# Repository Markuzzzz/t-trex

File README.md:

# t-trex
Python based quadruped robot powered by Raspberry Pi Zero 2 W

# nifty-inspirations
Nifty Projects - because simple solutions are hard to find!

## Description

t-trex for Raspberry Pi is based on the [Sunfounder Remote Control Crawling Robot](https://www.elektormagazine.com/news/review-sunfounder-remote-control-crawling-quadruped-robot-v2-0) by panerqiang@sunfounder.com, which was the main starting point of the Python code for this project. Especially the calculations related to kinematics of the legs was very helpful. [Regis Hsu](https://www.instructables.com/DIY-Spider-RobotQuad-robot-Quadruped/) on his turn created an amazing 3D printed Quadruped frame which was also based on the Sunfounder project. t-trex is fundamentally built on the work of these two projects to jumpstart and extend with new features. The code written in C was ported to Python and fully refactored, because this programming language is focussed more on the ease of development. So easy to step in for beginners. And when Python is not fast enough (like compiled C code is), it can be combined with the low level C-language. Python is also very popular in the AI community and embedded solutions, resulting in massive amount of libraries to your disposal. Last but not least, Python is also very well supported by the Raspberry Pi ecosystem. 

More to come soon, as I will upload resources to github!

## Features
- Fully Python 3 compatible

- Remote SSH over Wifi support

- PS4 Controller support ([python-evdev](https://python-evdev.readthedocs.io/en/latest/))
    * Crawling Gait Control
    * Speed up/down movements
    * Graceful Quit Program Hard Shutdown (mode 1 soft shutdown)
    * Rumble support
    * System report (mode 1 default stance)

- Different Crwaling Gaits implemented
    * Forward 
    * Backward
    * Left
    * Right
    * Stand (mode 1 head up)
    * Sit (mode 1 head down)
    * Head up/down

- PiJuice Zero Hat
    * Monitoring by PiJuice Zero for save shutdown on low battery voltage
    * custom led usage for simple messages
    * custom switch support for shutting down RPi OS 

- Systemd bootable service (sequence)
    * Logging to System Journal
    * Automatic reconnect at startup
    * Graceful Shutdown sequence on exception

To do
- Interruptable actions
- Advanced movements using analog joysticks
- AI Supervised Neural Net

# Video's of the different build phases
Phase 1: Re-creating Regis Hsu quadruped setup with the Arduino code.

https://user-images.githubusercontent.com/20856694/191291677-cc345581-42a2-487b-9b4e-a81b1ac22a6e.mov

Phase 2: Redesigned model and converted Arduino code to Python
#todo add

## Hardware Configuration
At the heart of this robot runs a RPi Zero W 2 as main cpu. Its controls 12 SG90 micro servo’s distributed over 4 legs using a I2C Servo PWM Pi (made by ABElectronics). To drive the power hungry micro servo’s, the power system consists of two separate power supplies to prevent voltage dips. One dedicated 1S LiPo @ 500 mAh for the RPi, fully managed by a PiJuice module on top of the RPi. Which is also able to charge the LiPo in place by USB or solar power source. The micro servo’s have their own power supply using a 2S LiPo @ 1300 mAh through a 5V buck converter for heavy duty action.

## Components
[Raspberry Pi Zero 2 W](https://www.raspberrypi.com/products/raspberry-pi-zero-2-w/) - the heart of the quadruped robot

[Servo PWM Driver Pi Zero](https://www.abelectronics.co.uk/p/72/servo-pwm-pi-zero) - Servo driver for all 12 servo's

[SG90 Servo](https://www.kiwi-electronics.com/nl/micro-servo-sg90-1-8kg-cm-9g-3018) - Servo type used

[UBEC DC/DC Step-Down Buck Converter - 5V/3A](https://www.kiwi-electronics.com/nl/ubec-dc-dc-step-down-buck-converter-5v-3a-output-9976) - Stepping down 2S 7.8V to 5V converter used for the 12 servo's and servo driver

[Pi-Juice Zero Hat](https://github.com/PiSupply/PiJuice) - Uninterruptable Power Supply (UPS) for the raspberry pi only, to ensure correct execution

[2S LiPo 1300 mAh](https://www.velleman.eu/products/view/?id=434062) - Battery used for servo system with built-in Battery Management System (BMS)

[1S LiPo 500 mAh](https://uk.pi-supply.com/products/lithium-ion-polymer-battery-3-7v-500mah) - Battery used for PiJuice and Raspberry Pi Zero 2 W with BMS

## Body Framework
The body is based on the work of [Regis Hsu](https://www.instructables.com/DIY-Spider-RobotQuad-robot-Quadruped/). To fit my chosen LiPo batteries, I altered his model. This is added to the design models.

## Installation
[Setup Pi Zero 2 W](https://desertbot.io/blog/headless-raspberry-pi-zero-w-2-ssh-wifi-setup-mac-windows-10-steps) - how to setup a headless RPi, this project uses Raspbian OS Lite Legacy 2022-01-28

```bash
# Python3 setup
sudo apt install -y python3-dev
sudo apt install -y python3-smbus i2c-tools
sudo apt install -y python3-pil
sudo apt install -y python3-pip
sudo apt install -y python3-setuptools
sudo apt install -y python3-rpi.gpio

# Evdev 
sudo pip install evdev

# Pijuice Zero
sudo apt-get install pijuice-base

# Servo driver library
git clone https://github.com/abelectronicsuk/ABElectronics_Python_Libraries.git
sudo python3 setup.py install

# PS4 Controller
sudo apt-get install joystick
```

## Additional Commands
```bash
# Increase Swap file 
df -Bm # check free space available
sudo dphys-swapfile swapoff
sudo nano /etc/dphys-swapfile
# Change Swap size
sudo dphys-swapfile setup
sudo dphys-swapfile swapon
sudo reboot now

# Prevent ssh ‘hang’ in terminal
Host ttrex.local
  HostName ttrex.local
  User markus
  ServerAliveInterval 10

# SSH connection set in terminal per server 
Sudo nano ~/.ssh/config
Host keepsdroppingme.com
   ServerAliveInterval 10

For killing it when it gets hang up, you can use the ssh escape character: ~.

# Connect to bluetooth controller
sudo bluetoothctl
agent on
discoverable on
pairable on
default-agent

Scan on
Pair <device id>
Trust <device id>
Connect <device id>

if not connecting, remove first!

# evdev testing
python3 /usr/local/lib/python3.9/dist-packages/evdev/evtest.py
Or
python3 -m evdev.evtest

# i2c commands
# change speed
sudo nano /boot/config.txt
dtparam=i2c_arm=on,i2c_arm_baudrate=200000

# check current clock speed
sudo cat /sys/kernel/debug/clk/clk_summary

# check i2c address layout
i2cdetect -y 1
i2cdetect -y -a 1 # detect outside range
```

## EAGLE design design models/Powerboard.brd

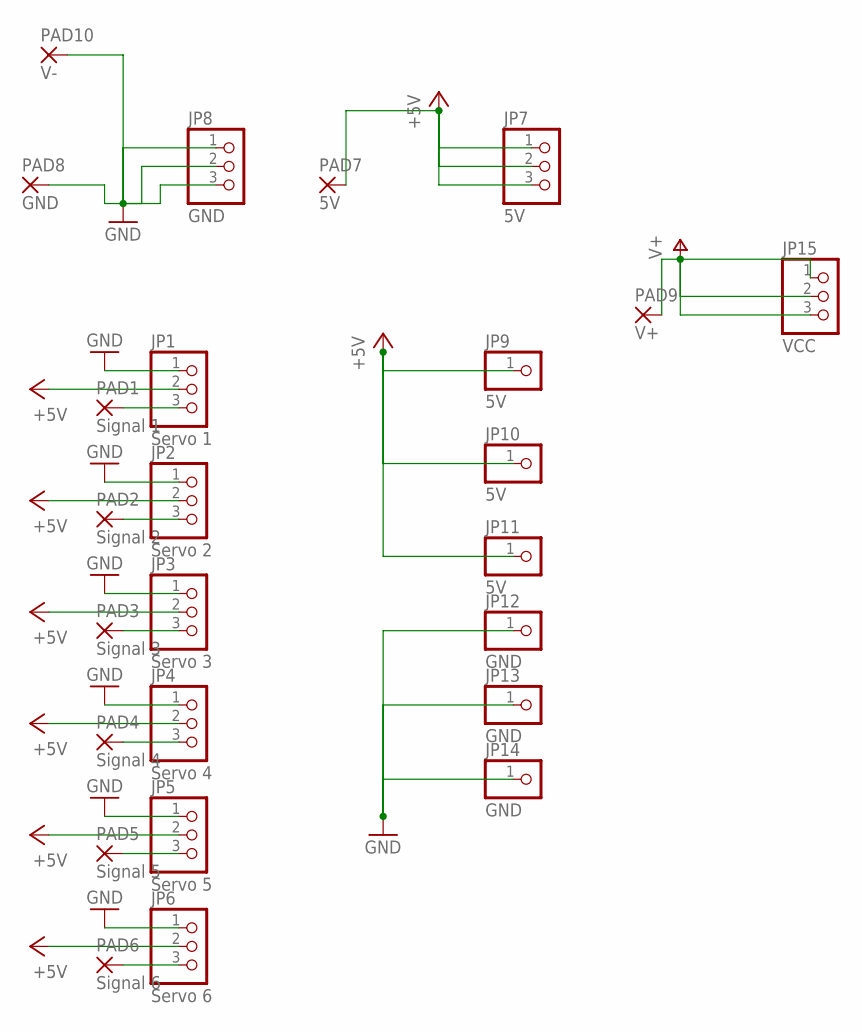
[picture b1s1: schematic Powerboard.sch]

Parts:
JP1: Servo 1; 1X03
JP2: Servo 2; 1X03
JP3: Servo 3; 1X03
JP4: Servo 4; 1X03
JP5: Servo 5; 1X03
JP6: Servo 6; 1X03
JP7: 5V; 1X03
JP8: GND; 1X03
JP9, JP10, JP11: 5V; 1X01
JP12, JP13, JP14: GND; 1X01
JP15: VCC; 1X03
PAD1: Signal 1; 3,81/1,4
PAD2: Signal 2; 3,81/1,4
PAD3: Signal 3; 3,81/1,4
PAD4: Signal 4; 3,81/1,4
PAD5: Signal 5; 3,81/1,4
PAD6: Signal 6; 3,81/1,4
PAD7: 5V; 3,81/1,4
PAD8: GND; 3,81/1,4
PAD9: V+; 3,81/1,4
PAD10: V-; 3,81/1,4

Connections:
+5V: JP1.2, JP2.2, JP3.2, JP4.2, JP5.2, JP6.2, JP7.1, JP7.2, JP7.3, JP9.1, JP10.1, JP11.1, PAD7.1
GND: JP1.1, JP2.1, JP3.1, JP4.1, JP5.1, JP6.1, JP8.1, JP8.2, JP8.3, JP12.1, JP13.1, JP14.1, PAD8.1, PAD10.1
unnamed: JP1.3, PAD1.1
unnamed: JP2.3, PAD2.1
unnamed: JP3.3, PAD3.1
unnamed: JP4.3, PAD4.1
unnamed: JP5.3, PAD5.1
unnamed: JP6.3, PAD6.1
V+: JP15.1, JP15.2, JP15.3, PAD9.1

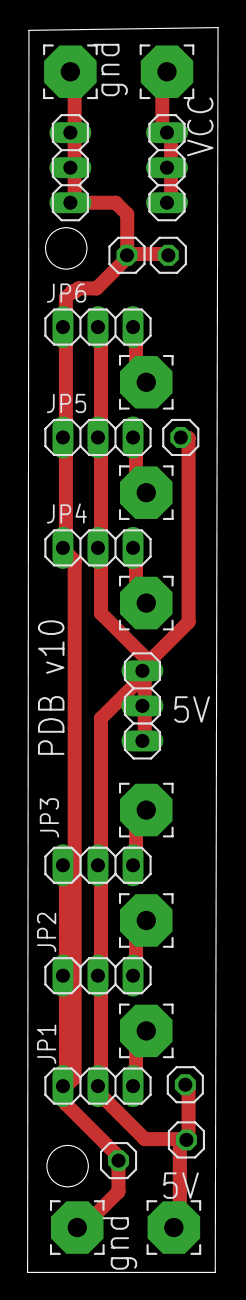
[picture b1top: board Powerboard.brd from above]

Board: 2 copper layers, 13.8 x 90.2 mm, 25 parts (0 on the bottom side), 9 nets.

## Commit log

2022-09-19 INITIAL_RELEASE
2024-11-01 Update LICENSE
